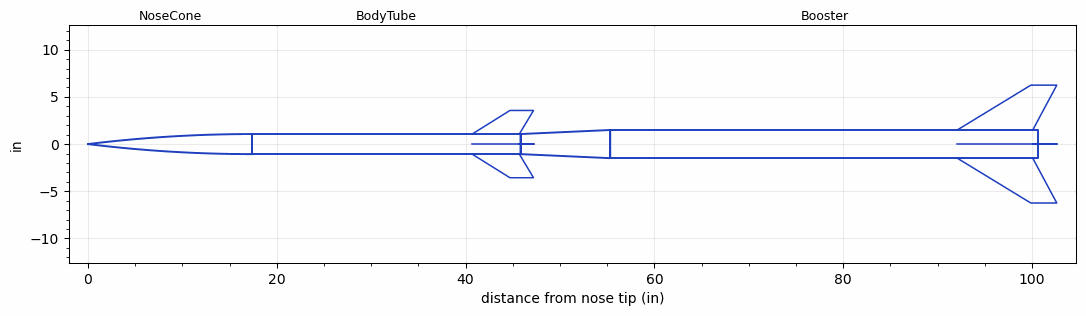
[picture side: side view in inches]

<RASAeroDocument>
 <FileVersion>2</FileVersion>
 <RocketDesign>
  <NoseCone>
   <Length>17.375</Length>
   <Diameter>2.125</Diameter>
   <Shape>Tangent Ogive</Shape>
   <Location>0</Location>
  </NoseCone>
  <BodyTube>
   <Length>28.443</Length>
   <Diameter>2.125</Diameter>
   <Location>17.375</Location>
   <Fin>
    <Count>4</Count>
    <Chord>5</Chord>
    <Span>2.5</Span>
    <SweepDistance>4</SweepDistance>
    <TipChord>2.5</TipChord>
    <Thickness>0.125</Thickness>
    <Location>5.125</Location>
    <AirfoilSection>Hexagonal</AirfoilSection>
    <FX1>2</FX1>
    <FX3>2</FX3>
   </Fin>
  </BodyTube>
  <Booster>
   <Length>45.366</Length>
   <Diameter>2.985</Diameter>
   <InsideDiameter>2.125</InsideDiameter>
   <Location>45.818</Location>
   <ShoulderLength>9.5</ShoulderLength>
   <Fin>
    <Count>4</Count>
    <Chord>8</Chord>
    <Span>4.75</Span>
    <SweepDistance>7.794</SweepDistance>
    <TipChord>2.75</TipChord>
    <Thickness>0.18</Thickness>
    <LERadius>0.1</LERadius>
    <Location>8.6</Location>
    <AirfoilSection>Hexagonal</AirfoilSection>
    <FX1>2</FX1>
    <FX3>2</FX3>
   </Fin>
  </Booster>
  <Surface>Rough Camouflage Paint</Surface>
  <ModifiedBarrowman>True</ModifiedBarrowman>
  <Turbulence>True</Turbulence>
  <UseBooster1>False</UseBooster1>
  <UseBooster2>False</UseBooster2>
 </RocketDesign>
 <LaunchSite>
  <Altitude>1344</Altitude>
  <Pressure>30</Pressure>
  <RodAngle>0</RodAngle>
  <RodLength>10</RodLength>
  <Temperature>38.51</Temperature>
  <WindSpeed>0</WindSpeed>
 </LaunchSite>
 <Recovery>
  <Altitude1>1000</Altitude1>
  <Altitude2>1500</Altitude2>
  <DeviceType1>Parachute</DeviceType1>
  <DeviceType2>Parachute</DeviceType2>
  <Event1>True</Event1>
  <Event2>True</Event2>
  <Size1>9</Size1>
  <Size2>36</Size2>
  <EventType1>Apogee</EventType1>
  <EventType2>Altitude</EventType2>
  <CD1>0.8</CD1>
  <CD2>0.8</CD2>
 </Recovery>
 <SimulationList>
  <Simulation>
   <SustainerEngine>K2144  (SRT)</SustainerEngine>
   <SustainerLaunchWt>5.51</SustainerLaunchWt>
   <SustainerCG>29.52</SustainerCG>
   <SustainerIgnitionDelay>0.5</SustainerIgnitionDelay>
   <Booster1Engine>M3464LB  (Loki)</Booster1Engine>
   <Booster1LaunchWt>24.7</Booster1LaunchWt>
   <Booster1SeparationDelay>0</Booster1SeparationDelay>
   <Booster1IgnitionDelay>0</Booster1IgnitionDelay>
   <Booster1CG>68.32</Booster1CG>
   <IncludeBooster1>True</IncludeBooster1>
   <Booster2Delay>0</Booster2Delay>
   <IncludeBooster2>False</IncludeBooster2>
   <TimetoApogee>37.30025</TimetoApogee>
   <MaxAltitude>38804.01</MaxAltitude>
   <MaxVelocity>4122.929</MaxVelocity>
  </Simulation>
 </SimulationList>
</RASAeroDocument>
